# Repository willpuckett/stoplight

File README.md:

# 🚥 Stoplight

### Features

- TMC2209 Stepper Driver
- 1 Ω Sense Resistors (tuned for small motors)
- HUSB238 PD Controller for dynamic Voltage Control
- On-board temperature sensing

Stoplight is a Xiao shield for operating small stepper motors. It is designed
specifically for 28-BYJ48, although it _may_ work with other small (0.225 RMS Amps or less) steppers as
well. It aims to provide utility all around the home, and is especially useful
when working with blinds and knobs.

Commercial stepsticks have sense resistors that are not properly sized for
'smaller' motors to take advantage of TMC2209's features, including
stallguard.

> StopLight brings stall sensing to commodity/low cost, high torque motors.

Stoplight seeks to remedy these issues, while also providing software selectable
voltage control and temperature measurement in a package that works well with
HomeAssistant/ESPHome.

### Todo 

- [ ] TVS Protection
- [ ] Change C14 to same as C18 (BOM Consolidation)
- [ ] Consider removing DIAG and just using UART events instead
- [ ] Consider reconneacting fan port
- [ ] Address DS18B20U reading high 
- [ ] Test fit in mini blind housing
- [ ] Dim LED brightness
- [x] Test StallGuard tuning
  - ✅ works very well at 12v+
  - ⚠️ 9v is untested 
  - 🚦 5v is more finicky
- [x] Add esphome sample yaml's

## Homing

## Fabrication

Use the [production files](jlcpcb/production_files/) to upload to jlc. Or first run [available here](https://octule.com/listing/1891073906/stoplight).

You'll need to swap the motor wires to a JST XH 4 pin housing. In addition to
removing the red cable, you also **must** perform the
[bipolar mod](https://ardufocus.com/howto/28byj-48-bipolar-hw-mod/) on your
steppers.

## Example HomeAssistant Config

The build sometimes fails, but can usually be completed by repeatedly pressing
'Retry', or switching to 'arduino' framework.

### Tuning

<details><summary>This demo exposes a number of controls to make tuning StallGuard easier.</summary>

```yaml
substitutions:
  name: "stoplight"
  friendly_name: "StopLight"
  board: "seeed_xiao_esp32c3"

# board/wifi/ota stuff
packages:
  device_base: !include .esp32.yaml

esp32:
  framework:
    type: esp-idf

logger:
  level: DEBUG

esphome:
  on_boot:
    - tmc2209.configure:
        direction: cw # or ccw
        microsteps: 1
        interpolation: True
        enable_spreadcycle: False
        tcool_threshold: 0
        tpwm_threshold: 0
    - tmc2209.stallguard:
        threshold: 23
    - tmc2209.currents:
        standstill_mode: freewheeling
        run_current: 0.150 # was 0.240
        hold_current: 0
    - button.press: home # home right after boot

external_components:
  - source: github://slimcdk/esphome-custom-components
    components: [tmc2209_hub, tmc2209, stepper]
  - source: github://pr#6693
    components: [husb238]

globals:
  - id: has_homed
    type: bool
    initial_value: "true"
    restore_value: no
  - id: homing_speed
    type: int
    initial_value: "480"
    restore_value: True

web_server:
  port: 80

i2c:
  sda: GPIO6
  scl: GPIO7
  frequency: 800kHz

uart:
  tx_pin: GPIO21
  rx_pin: GPIO20
  baud_rate: 500000 # 9600 -> 500k

one_wire:
  - platform: gpio
    pin: GPIO10

stepper:
  - platform: tmc2209
    id: driver
    # https://www.klipper3d.org/TMC_Drivers.html#limitations
    max_speed: 2000 steps/s # was 4000
    acceleration: 1000 steps/s^2 # was 2500
    deceleration: 1000 steps/s^2 # was 2500
    index_pin: GPIO3
    diag_pin: GPIO4
    rsense: 1000 mOhm
    config_dump_include_registers: False
    vsense: False
    analog_current_scale: False
    on_stall:
      - logger.log: "Motor stalled!"
      - if:
          condition:
            lambda: return !id(has_homed);
          then:
            - stepper.stop: driver
            - tmc2209.configure:
                direction: cw # or ccw
                microsteps: 1
                interpolation: True
                enable_spreadcycle: False
                tcool_threshold: 0
            - stepper.report_position:
                id: driver
                position: 0
            - globals.set:
                id: has_homed
                value: "true"
            - logger.log: "Home position set"
            - tmc2209.disable
    on_status:
      - logger.log:
          format: "Driver is reporting an update! (code %d)"
          args: ["code"]
      - if:
          condition:
            lambda: return code == tmc2209::DIAG_TRIGGERED;
          then:
            - logger.log: DIAG_TRIGGERED
      - if:
          condition:
            lambda: return code == tmc2209::DIAG_TRIGGER_CLEARED;
          then:
            - logger.log: DIAG_TRIGGER_CLEARED
      - if:
          condition:
            lambda: return code == tmc2209::RESET;
          then:
            - logger.log: RESET
      - if:
          condition:
            lambda: return code == tmc2209::RESET_CLEARED;
          then:
            - logger.log: RESET_CLEARED
      - if:
          condition:
            lambda: return code == tmc2209::DRIVER_ERROR;
          then:
            - logger.log: DRIVER_ERROR
      - if:
          condition:
            lambda: return code == tmc2209::DRIVER_ERROR_CLEARED;
          then:
            - logger.log: DRIVER_ERROR_CLEARED
      - if:
          condition:
            lambda: return code == tmc2209::CP_UNDERVOLTAGE;
          then:
            - logger.log: CP_UNDERVOLTAGE
      - if:
          condition:
            lambda: return code == tmc2209::CP_UNDERVOLTAGE_CLEARED;
          then:
            - logger.log: CP_UNDERVOLTAGE_CLEARED
      - if:
          condition:
            lambda: return code == tmc2209::OVERTEMPERATURE_PREWARNING;
          then:
            - logger.log: OVERTEMPERATURE_PREWARNING
      - if:
          condition:
            lambda: return code == tmc2209::OVERTEMPERATURE_PREWARNING_CLEARED;
          then:
            - logger.log: OVERTEMPERATURE_PREWARNING_CLEARED
      - if:
          condition:
            lambda: return code == tmc2209::OVERTEMPERATURE;
          then:
            - logger.log: OVERTEMPERATURE
      - if:
          condition:
            lambda: return code == tmc2209::OVERTEMPERATURE_CLEARED;
          then:
            - logger.log: OVERTEMPERATURE_CLEARED
      - if:
          condition:
            lambda: return code == tmc2209::TEMPERATURE_ABOVE_120C;
          then:
            - logger.log: TEMPERATURE_ABOVE_120C
      - if:
          condition:
            lambda: return code == tmc2209::TEMPERATURE_BELOW_120C;
          then:
            - logger.log: TEMPERATURE_BELOW_120C
      - if:
          condition:
            lambda: return code == tmc2209::TEMPERATURE_ABOVE_143C;
          then:
            - logger.log: TEMPERATURE_ABOVE_143C
      - if:
          condition:
            lambda: return code == tmc2209::TEMPERATURE_BELOW_143C;
          then:
            - logger.log: TEMPERATURE_BELOW_143C
      - if:
          condition:
            lambda: return code == tmc2209::TEMPERATURE_ABOVE_150C;
          then:
            - logger.log: TEMPERATURE_ABOVE_150C
      - if:
          condition:
            lambda: return code == tmc2209::TEMPERATURE_BELOW_150C;
          then:
            - logger.log: TEMPERATURE_BELOW_150C
      - if:
          condition:
            lambda: return code == tmc2209::TEMPERATURE_ABOVE_157C;
          then:
            - logger.log: TEMPERATURE_ABOVE_157C
      - if:
          condition:
            lambda: return code == tmc2209::TEMPERATURE_BELOW_157C;
          then:
            - logger.log: TEMPERATURE_BELOW_157C
      - if:
          condition:
            lambda: return code == tmc2209::OPEN_LOAD;
          then:
            - logger.log: OPEN_LOAD
      - if:
          condition:
            lambda: return code == tmc2209::OPEN_LOAD_CLEARED;
          then:
            - logger.log: OPEN_LOAD_CLEARED
      - if:
          condition:
            lambda: return code == tmc2209::OPEN_LOAD_A;
          then:
            - logger.log: OPEN_LOAD_A
      - if:
          condition:
            lambda: return code == tmc2209::OPEN_LOAD_A_CLEARED;
          then:
            - logger.log: OPEN_LOAD_A_CLEARED
      - if:
          condition:
            lambda: return code == tmc2209::OPEN_LOAD_B;
          then:
            - logger.log: OPEN_LOAD_B
      - if:
          condition:
            lambda: return code == tmc2209::OPEN_LOAD_B_CLEARED;
          then:
            - logger.log: OPEN_LOAD_B_CLEARED
      - if:
          condition:
            lambda: return code == tmc2209::LOW_SIDE_SHORT;
          then:
            - logger.log: LOW_SIDE_SHORT
      - if:
          condition:
            lambda: return code == tmc2209::LOW_SIDE_SHORT_CLEARED;
          then:
            - logger.log: LOW_SIDE_SHORT_CLEARED
      - if:
          condition:
            lambda: return code == tmc2209::LOW_SIDE_SHORT_A;
          then:
            - logger.log: LOW_SIDE_SHORT_A
      - if:
          condition:
            lambda: return code == tmc2209::LOW_SIDE_SHORT_A_CLEARED;
          then:
            - logger.log: LOW_SIDE_SHORT_A_CLEARED
      - if:
          condition:
            lambda: return code == tmc2209::LOW_SIDE_SHORT_B;
          then:
            - logger.log: LOW_SIDE_SHORT_B
      - if:
          condition:
            lambda: return code == tmc2209::LOW_SIDE_SHORT_B_CLEARED;
          then:
            - logger.log: LOW_SIDE_SHORT_B_CLEARED
      - if:
          condition:
            lambda: return code == tmc2209::GROUND_SHORT;
          then:
            - logger.log: GROUND_SHORT
      - if:
          condition:
            lambda: return code == tmc2209::GROUND_SHORT_CLEARED;
          then:
            - logger.log: GROUND_SHORT_CLEARED
      - if:
          condition:
            lambda: return code == tmc2209::GROUND_SHORT_A;
          then:
            - logger.log: GROUND_SHORT_A
      - if:
          condition:
            lambda: return code == tmc2209::GROUND_SHORT_A_CLEARED;
          then:
            - logger.log: GROUND_SHORT_A_CLEARED
      - if:
          condition:
            lambda: return code == tmc2209::GROUND_SHORT_B;
          then:
            - logger.log: GROUND_SHORT_B
      - if:
          condition:
            lambda: return code == tmc2209::GROUND_SHORT_B_CLEARED;
          then:
            - logger.log: GROUND_SHORT_B_CLEARED

button:
  - platform: template
    name: Home
    id: home
    on_press:
      - logger.log: "Going home!"
      - tmc2209.configure:
          direction: cw # or ccw
          microsteps: 1
          interpolation: True
          enable_spreadcycle: False
          tcool_threshold: 104
          tpwm_threshold: 0
      # - lambda: id(driver)->write_register(TPWMTHRS, 0);
      # - lambda: id(driver)->write_register(TCOOLTHRS, 1048575);
      - globals.set:
          id: has_homed
          value: "false"
      - stepper.set_speed:
          id: driver
          # 60 to 300 rpm
          speed: !lambda return id(homing_speed);
      - stepper.set_target:
          id: driver
          target: -9999999
  - platform: template
    name: Stop
    id: stop
    on_press:
      - logger.log: "Stopping!"
      - stepper.stop: driver
      - tmc2209.disable
  - platform: template
    name: 1000 Steps forward
    on_press:
      - logger.log: "Going forward!"
      - stepper.set_speed:
          id: driver
          speed: 400 steps/s
      - stepper.set_target:
          id: driver
          target: !lambda return id(driver)->current_position +1000;
      # - tmc2209.disable

husb238:
  id: husb_01

binary_sensor:
  - platform: husb238
    attached: "PD Attached"

  - platform: template
    name: "Has Homed"
    lambda: return id(has_homed);

text_sensor:
  - platform: husb238
    status: "Last request status"
    capabilities: "Capabilities"

select:
  - platform: husb238
    voltage: "Voltage selector"

sensor:
  - platform: husb238
    voltage: "Contracted Voltage"
    current: "Contracted Current"
    selected_voltage: "Selected Voltage"

  - platform: dallas_temp
    name: temperature

  - platform: tmc2209
    type: stallguard_result
    name: Driver stallguard
    update_interval: 10s

  - platform: tmc2209
    type: actual_current
    name: Actual current
    update_interval: 10s

  - platform: tmc2209
    type: motor_load
    name: Motor load
    update_interval: 10s

  # - platform: tmc2209
  #   type: pwm_scale_sum
  #   name: PWM Scale Sum
  #   update_interval: 250ms

  # - platform: tmc2209
  #   type: pwm_scale_auto
  #   name: PWM Scale Auto
  #   update_interval: 250ms

  # - platform: tmc2209
  #   type: pwm_ofs_auto
  #   name: PWM OFS Auto
  #   update_interval: 250ms

  # - platform: tmc2209
  #   type: pwm_grad_auto
  #   name: PWM Grad Auto
  #   update_interval: 250ms

number:
  - platform: template
    name: Target position
    min_value: -999999
    max_value: 999999
    step: 100
    lambda: return id(driver)->current_position;
    update_interval: 10s
    set_action:
      - stepper.set_target:
          id: driver
          target: !lambda "return x;"

  - platform: template
    name: Homing RPM
    min_value: 0
    max_value: 300
    step: 1
    lambda: return id(homing_speed) * 60 / 32;
    update_interval: 10s
    set_action:
      - globals.set:
          id: homing_speed
          value: !lambda "return x * 32 / 60;"

  - platform: template
    name: SGTHRS
    min_value: 0
    max_value: 255
    step: 1
    lambda: return id(driver)->read_register(SGTHRS);
    update_interval: 10s
    set_action:
      - lambda: id(driver)->write_register(SGTHRS, x);

  - platform: template
    name: TCOOLTHRS
    min_value: 0
    max_value: 1048575
    step: 1
    lambda: return id(driver)->read_register(TCOOLTHRS);
    update_interval: 10s
    set_action:
      - lambda: id(driver)->write_register(TCOOLTHRS, x);

  - platform: template
    name: "Run Current"
    min_value: 0
    max_value: 31
    step: 1
    lambda: return id(driver)->read_field(IRUN_FIELD);
    update_interval: 10s
    set_action:
      - tmc2209.currents:
          irun: !lambda "return x;"
```
</details>

### Wall Heater

<details><summary>This demo implements a knob controlled wall heater.</summary>

```yaml
substitutions:
  name: "heater"
  friendly_name: "Wall Heater"
  board: "seeed_xiao_esp32c3"

# board/wifi/ota stuff
packages:
  device_base: !include .esp32.yaml

esphome:
  on_boot:
    # - lambda: id(husb_01)->command_request_voltage(5);
    - tmc2209.configure:
        direction: cw # or ccw
        microsteps: 1
        interpolation: True
        enable_spreadcycle: False
        tcool_threshold: 0
        tpwm_threshold: 0
    - tmc2209.stallguard:
        threshold: 23
    - tmc2209.currents:
        standstill_mode: freewheeling
        run_current: 0.1375 # was 0.150
        hold_current: 0
    - button.press: probe_low # home right after boot

external_components:
  - source: github://slimcdk/esphome-custom-components
    components: [ tmc2209_hub, tmc2209, stepper ]
  - source: github://pr#6693
    components: [ husb238 ]

globals:
  - id: steps
    type: int
    restore_value: yes
    initial_value: "1000"

i2c:
  sda: GPIO6
  scl: GPIO7 
  frequency: 800kHz

uart:
  tx_pin: GPIO21
  rx_pin: GPIO20
  baud_rate: 500000 # 9600 -> 500k

one_wire:
  - platform: gpio
    pin: GPIO10

husb238:
  id: husb_01

stepper:
  - platform: tmc2209
    id: driver
    max_speed: 480 steps/s
    acceleration: 1000 steps/s^2 
    deceleration: 1000 steps/s^2 
    index_pin: GPIO3
    diag_pin: GPIO4
    rsense: 1000 mOhm
    on_stall:
      - stepper.stop: driver
      - logger.log: Endstop Detected 🍍

script:
  - id: move_stepper
    mode: restart
    parameters:
      # use 0/false for low side endstop, 1/true for high side
      homing: bool
      target: int
    then:
      - lambda: id(husb_01)->command_request_voltage(20);
      - tmc2209.configure:
          tcool_threshold: !lambda 'return homing ? 104 : 0;'
      - stepper.set_speed:
          id: driver
          speed: 480 steps/s
      - delay: 1s
      - stepper.set_target:
          id: driver
          target: !lambda 'return target;'
      - wait_until:
          condition:
            lambda: 'return id(driver)->has_reached_target();'
      - logger.log:
          format: "Moved to %d steps"
          args: [ 'id(driver)->current_position' ]
      - tmc2209.disable:
          id: driver 
      - lambda: id(husb_01)->command_request_voltage(5);

button:
  - platform: template
    name: Probe Low
    id: probe_low 
    on_press:
      - climate.control:
          id: pid_climate
          mode: 'OFF'
      - script.execute: 
          id: move_stepper
          homing: true
          target: -9999999
      - script.wait: move_stepper
      - stepper.report_position:
          id: driver
          position: 0
      - logger.log:
          format: "Probed to %d steps"
          args: [ 'id(driver)->current_position' ]
      
  - platform: template
    name: Probe High
    id: probe_high
    on_press:
      - climate.control:
          id: pid_climate
          mode: 'OFF'
      - script.execute: 
          id: move_stepper
          homing: true
          target: 9999999
      - script.wait: move_stepper
      - globals.set:
          id: steps
          value: !lambda 'return id(driver)->current_position;'
 
  - platform: template
    name: "PID Climate Autotune"
    on_press:
      - climate.pid.autotune: pid_climate

sensor:
  - platform: husb238
    voltage: "Contracted Voltage"

  - platform: template
    name: "Steps"
    id: steps_display
    icon: "mdi:shoe-print"
    accuracy_decimals: 0
    lambda: 'return id(steps);'

  - platform: dallas_temp
    id: ds_temp
    filters: 
      - lambda: return x - 13.5;

  # This sensor takes the output from the pid heater and transforms it to step numbers
  - platform: pid
    name: "PID Climate Heat"
    id: heat_float
    type: HEAT
    filters:
      - round_to_multiple_of: 10
      - delta: 9
    on_value:
      then:
        - script.execute: 
            id: move_stepper
            homing: false
            target: !lambda 'return static_cast<int>(id(steps) * (x / 100));'

# This is just a fake output to make the pid heater happy.
# Ideally, the pin will use the onboard led, but I'm not sure what the pin number is for that...
output:
  - platform: ledc
    pin: GPIO2
    id: heater_output

# Example configuration entry
climate:
  - platform: pid
    name: "PID Climate Controller"
    id: pid_climate
    sensor: ds_temp
    default_target_temperature: 21°C
    heat_output: heater_output
    control_parameters:
      kp: 4
      ki: 0.4
      kd: 0.5
      output_averaging_samples: 5      # smooth the output over 5 samples
      derivative_averaging_samples: 5  # smooth the derivative value over 5 samples
    # deadband_parameters:
    #   threshold_high: 0.5°C
    #   threshold_low: -1.0°C
    #   kp_multiplier: 0.5   # proportional gain reduced inside deadband
    #   ki_multiplier: 0.25   # integral accumulates at only 25% of normal ki
    #   kd_multiplier: 0.5   # derviative is reduced inside deadband
    #   deadband_output_averaging_samples: 5   # average the output over 15 samples within the deadband
```

</details>

### Blinds

<details><summary>StallGuard blinds operation</summary>

```yaml
substitutions:
  name: "blins03"
  blind_number: right
  friendly_name: "Right Blind"
  board: "seeed_xiao_esp32c3"
  delay: "1s"

# board/wifi/ota stuff
packages:
  device_base: !include .esp32.yaml

esphome:
  on_boot:
    - tmc2209.configure:
        direction: ccw # or ccw
        microsteps: 1
        interpolation: True
        enable_spreadcycle: False
        tcool_threshold: 0
        tpwm_threshold: 0
    - tmc2209.stallguard:
        threshold: 45 
    - tmc2209.currents:
        standstill_mode: freewheeling
        run_current: 0.1375 # was 0.150
        hold_current: 0

external_components:
  - source: github://slimcdk/esphome-custom-components
    components: [ tmc2209_hub, tmc2209, stepper ]
  - source: github://pr#6693
    components: [ husb238 ]

globals:
  - id: steps
    type: int
    restore_value: yes
    initial_value: "1000"

i2c:
  sda: GPIO6
  scl: GPIO7 
  frequency: 800kHz

uart:
  tx_pin: GPIO21
  rx_pin: GPIO20
  baud_rate: 500000 # 9600 -> 500k

one_wire:
  - platform: gpio
    pin: GPIO10

husb238:
  id: husb_01

stepper:
  - platform: tmc2209
    id: driver
    max_speed: 480 steps/s
    acceleration: 1000 steps/s^2 
    deceleration: 1000 steps/s^2 
    index_pin: GPIO3
    diag_pin: GPIO4
    rsense: 1000 mOhm
    on_stall:
      - stepper.stop: driver
      - logger.log: Endstop Detected 🍍

script:
  - id: move_stepper
    mode: restart
    parameters:
      # use 0/false for low side endstop, 1/true for high side
      homing: bool
      target: int
    then:
      - lambda: id(husb_01)->command_request_voltage(12);
      - tmc2209.configure:
          tcool_threshold: !lambda 'return homing ? 104 : 0;'
      - stepper.set_speed:
          id: driver
          speed: !lambda 'return homing ? 480 : 120;'
      - delay: 1s
      - stepper.set_target:
          id: driver
          target: !lambda 'return target;'
      - while:
          condition:
            lambda: 'return !id(driver)->has_reached_target();'
          then:
            - cover.template.publish:
                id: ${name}_${blind_number}
                position: !lambda 'return float( id(driver).current_position ) / float( id(steps) );' 
                current_operation: !lambda 'return id(driver).current_position < id(driver).target_position ? COVER_OPERATION_OPENING : COVER_OPERATION_CLOSING;'
            - delay: ${delay}
      - logger.log:
          format: "Moved to %d steps"
          args: [ 'id(driver)->current_position' ]
      - tmc2209.disable:
          id: driver 
      - lambda: id(husb_01)->command_request_voltage(5);
      - cover.template.publish:
          id: ${name}_${blind_number}
          position: !lambda 'return float( id(driver).current_position ) / float( id(steps) );' 
          current_operation: IDLE

button:
  - platform: template
    name: Probe Low
    id: probe_low 
    on_press:
      - script.execute: 
          id: move_stepper
          homing: true
          target: -9999999
      - script.wait: move_stepper
      - stepper.report_position:
          id: driver
          position: 0
      - logger.log:
          format: "Probed to %d steps"
          args: [ 'id(driver)->current_position' ]
      
  - platform: template
    name: Probe High
    id: probe_high
    on_press:
      - script.execute: 
          id: move_stepper
          homing: true
          target: 9999999
      - script.wait: move_stepper
      - globals.set:
          id: steps
          value: !lambda 'return id(driver)->current_position;'

sensor:
  - platform: husb238
    voltage: "Contracted Voltage"

  - platform: template
    name: "Steps"
    id: steps_display
    icon: "mdi:shoe-print"
    accuracy_decimals: 0
    lambda: 'return id(steps);'

  - platform: dallas_temp
    id: ds_temp
    filters: 
      - lambda: return x - 13.5;

cover:
  - platform: template
    name: "${blind_number}"
    id: ${name}_${blind_number}
    open_action:
      then:
        - logger.log: "Opening"
        - button.press: probe_high
    close_action:
      then:
        - logger.log: "Closing"
        - button.press: probe_low
    position_action:
      then:
        - logger.log: "Jostling"
        - script.execute: 
            id: move_stepper
            homing: false
            target: !lambda return int(id(steps) * pos);
    stop_action:
      then:
        - script.execute: 
            id: move_stepper
            homing: false
            target: !lambda return id(driver).current_position;
    has_position: true
    device_class: blind

switch:
  - platform: template
    name: "Reset ${blind_number}"
    id: reset_${name}_${blind_number}
    turn_on_action:
      - button.press: probe_low
      - script.wait: move_stepper
      - button.press: probe_high
      - script.wait: move_stepper
      - button.press: probe_low
      - script.wait: move_stepper
      - switch.turn_off: reset_${name}_${blind_number}
```

</details>

## Schematic

## Reference

[TMC2209 Calaulations Worksheet](https://www.analog.com/media/en/engineering-tools/design-tools/TMC2209_Calculations.xlsx)

[BTT-TMC2209-v1.2](https://pax.deno.dev/bigtreetech/BIGTREETECH-TMC2209-V1.2@master/Schematic/TMC2209-V1.2.pdf?b)

[Cookie Robotics](https://cookierobotics.com/042/)

[jangeox](http://www.jangeox.be/2013/10/change-unipolar-28byj-48-to-bipolar.html)

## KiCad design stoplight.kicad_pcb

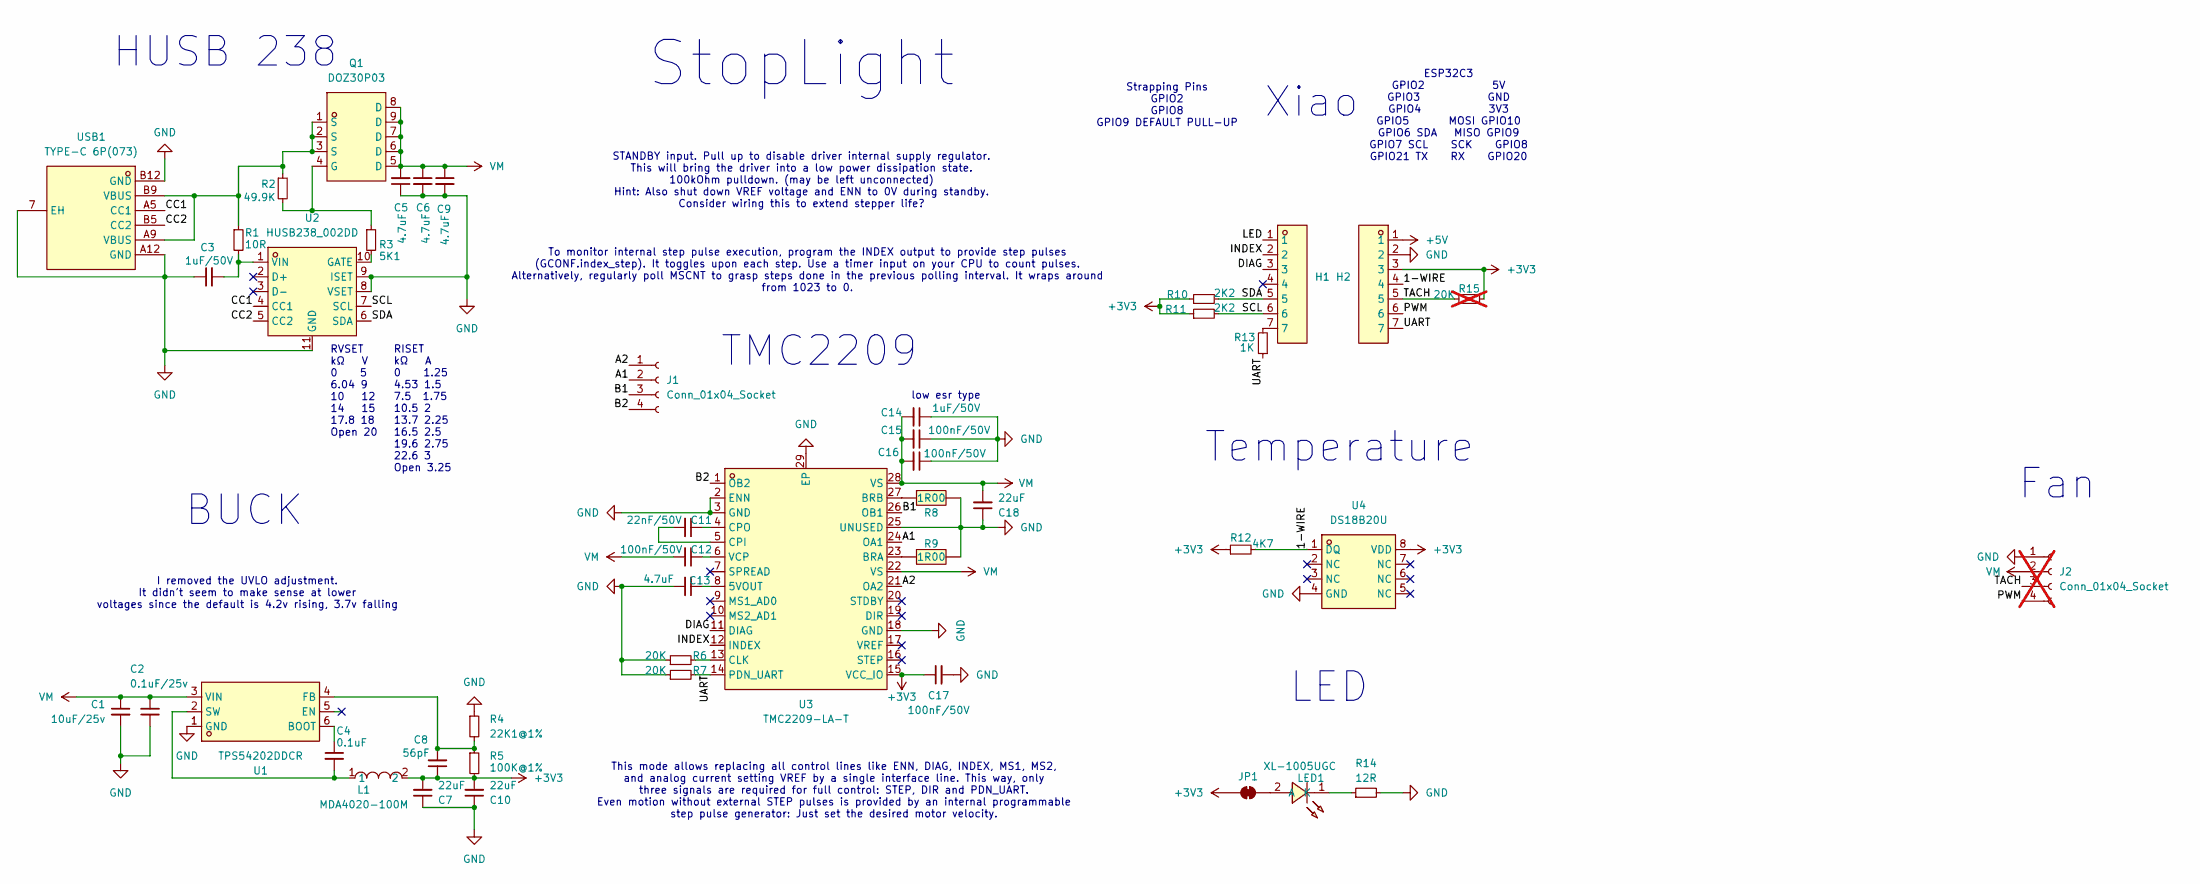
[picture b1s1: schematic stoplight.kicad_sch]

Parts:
C1: 10uF/25v; C_1210_3225Metric; LCSC C2918502
C2: 0.1uF/25v; C_0603_1608Metric; LCSC C3011652
C3: 1uF/50V; C_0805_2012Metric; LCSC C215803
C4: 0.1uF; C_0402_1005Metric; LCSC C77020
C5, C6, C9: 4.7uF; C_0805_2012Metric; LCSC C2991173
C7, C10, C18: 22uF; C_0805_2012Metric; LCSC Part C6119901
C8: 56pF; C_0402_1005Metric; LCSC C107007
C11: 22nF/50V; C_0402_1005Metric; LCSC C77023
C12, C15, C16, C17: 100nF/50V; C_0402_1005Metric; LCSC C77020
C13: 4.7uF; C_0603_1608Metric; LCSC C913474
C14: 1uF/50V; C_0603_1608Metric; LCSC C90540
H1, H2: MF254V-11-07-0743; HDR-TH_7P-P2.54-V-F_MF254V-11-07-0743; LCSC Part C2889988
J1: Conn_01x04_Socket; JST_XH_B4B-XH-A_1x04_P2.50mm_Vertical; LCSC C23398778
J2: Conn_01x04_Socket; FanPinHeader_1x04_P2.54mm_Vertical; not fitted
JP1: SolderJumper_2_Bridged; Solder_Jumper_Tight
L1: MDA4020-100M; IND-SMD_L4.5-W4.1_YXMAA0402; LCSC Part C2847473
LED1: XL-1005UGC; LED0402-RD_GREEN; LCSC Part C965793
Q1: DOZ30P03; PDFN-8_L3.1-W3.0-P0.65-LS3.3-BL; LCSC Part C36499166
R1: 10R; R_0603_1608Metric; LCSC C109318
R2: 49.9K; R_0603_1608Metric; LCSC C2930109
R3: 5K1; R_0603_1608Metric; LCSC C23186
R4: 22K1@1%; R_0402_1005Metric; LCSC C163478
R5: 100K@1%; R_0402_1005Metric; LCSC C60491
R6, R7: 20K; R_0402_1005Metric; LCSC C93942
R8, R9: 1R00; R0805; LCSC Part C346776
R10, R11: 2K2; R_0402_1005Metric; LCSC C114762
R12: 4K7; R_0402_1005Metric; LCSC C105871
R13: 1K; R_0603_1608Metric; LCSC C22548
R14: 12R; R_0402_1005Metric; LCSC Part C2909317
R15: 20K; R_0402_1005Metric; not fitted
U1: TPS54202DDCR; SOT-23-6_L2.9-W1.6-P0.95-LS2.8-BL; LCSC Part C191884
U2: HUSB238_002DD; DFN-10_L3.0-W3.0-P0.50-BL-EP2.5; LCSC Part C7471904
U3: TMC2209-LA-T; QFN-28_L5.0-W5.0-P0.50-BL-EP; LCSC Part C2150710
U4: DS18B20U; MSOP-8_L3.0-W3.0-P0.65-LS4.9-BL; LCSC Part C695836
USB1: TYPE-C 6P(073); TYPE-C-SMD_TYPE-C-6P_5; LCSC Part C668623

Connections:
+3V3: C7.2, C8.1, C10.2, C17.1, H2.3, JP1.1 (A), L1.2, R5.2, R10.1, R11.1, R12.1, R15.2, U3.15 (VCC_IO), U4.8 (VDD)
+5V: H2.1
/1-WIRE: H2.4, R12.2, U4.1 (DQ)
/A1: J1.2, U3.24 (OA1)
/A2: J1.1, U3.21 (OA2)
/B1: J1.3, U3.26 (OB1)
/B2: J1.4, U3.1 (OB2)
/CC1: U2.4 (CC1), USB1.A5 (CC1)
/CC2: U2.5 (CC2), USB1.B5 (CC2)
/DIAG: H1.3, U3.11 (DIAG)
/INDEX: H1.2, U3.12 (INDEX)
/LED: H1.1
/PWM: H2.6, J2.4
/SCL: H1.6, R11.2, U2.7 (SCL)
/SDA: H1.5, R10.2, U2.6 (SDA)
/TACH: H2.5, J2.3, R15.1
/UART: H2.7, R7.2, R13.1, U3.14 (PDN_UART)
GND: C1.2, C2.1, C3.1, C5.1, C6.2, C7.1, C9.2, C10.1, C13.2, C14.1, C15.1, C16.1, C17.2, C18.1, H2.2, J2.1, R4.1, R6.1, R7.1, R8.2, R9.2, R14.2, U1.1 (GND), U2.8 (VSET), U2.9 (ISET), U2.11 (GND), U3.2 (ENN), U3.3 (GND), U3.18 (GND), U3.25 (UNUSED), U3.29 (EP), U4.4 (GND), USB1.7 (EH), USB1.A12 (GND), USB1.B12 (GND)
unnamed: H1.7, R13.2
unnamed: JP1.2 (B), LED1.2 (A)
unnamed: LED1.1 (K), R14.1
unnamed: Q1.4 (G), R2.2, R3.1
unnamed: Q1.1 (S), Q1.2 (S), Q1.3 (S), R1.1, R2.1, USB1.A9 (VBUS), USB1.B9 (VBUS)
unnamed: C4.1, U1.6 (BOOT)
unnamed: C8.2, R4.2, R5.1, U1.4 (FB)
unnamed: C4.2, L1.1, U1.2 (SW)
unnamed: R3.2, U2.10 (GATE)
unnamed: C3.2, R1.2, U2.1 (VIN)
unnamed: C13.1, U3.8 (5VOUT)
unnamed: R9.1, U3.23 (BRA)
unnamed: R8.1, U3.27 (BRB)
unnamed: R6.2, U3.13 (CLK)
unnamed: C11.2, U3.5 (CPI)
unnamed: C11.1, U3.4 (CPO)
unnamed: C12.1, U3.6 (VCP)
VM: C1.1, C2.2, C5.2, C6.1, C9.1, C12.2, C14.2, C15.2, C16.2, C18.2, J2.2, Q1.5 (D), Q1.6 (D), Q1.7 (D), Q1.8 (D), Q1.9 (D), U1.3 (VIN), U3.22 (VS), U3.28 (VS)

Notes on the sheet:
Strapping Pins GPIO2 GPIO8 GPIO9 DEFAULT PULL-UP
Xiao
TMC2209
I removed the UVLO adjustment. It didn't seem to make sense at lower voltages since the default is 4.2v rising, 3.7v falling
STANDBY input. Pull up to disable driver internal supply regulator. This will bring the driver into a low power dissipation state. 100kOhm pulldown. (may be left unconnected) Hint: Also shut down VREF voltage and ENN to 0V during standby. Consider wiring this to extend stepper life?
low esr type
To monitor internal step pulse execution, program the INDEX output to provide step pulses (GCONF.index_step). It toggles upon each step. Use a timer input on your CPU to count pulses. Alternatively, regularly poll MSCNT to grasp steps done in the previous polling interval. It wraps around from 1023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
RVSET kΩ V 0 5 6.04 9 10 12 14 15 17.8 18 Open 20
StopLight
LED
Fan
RISET kΩ A 0 1.25 4.53 1.5 7.5 1.75 10.5 2 13.7 2.25 16.5 2.5 19.6 2.75 22.6 3 Open 3.25
This mode allows replacing all control lines like ENN, DIAG, INDEX, MS1, MS2, and analog current setting VREF by a single interface line. This way, only three signals are required for full control: STEP, DIR and PDN_UART. Even motion without external STEP pulses is provided by an internal programma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
Temperature
HUSB 238
BUCK
ESP32C3 GPIO2 5V GPIO3 GND GPIO4 3V3 GPIO5 MOSI GPIO10 GPIO6 SDA MISO GPIO9 GPIO7 SCL SCK GPIO8 GPIO21 TX RX GPIO20

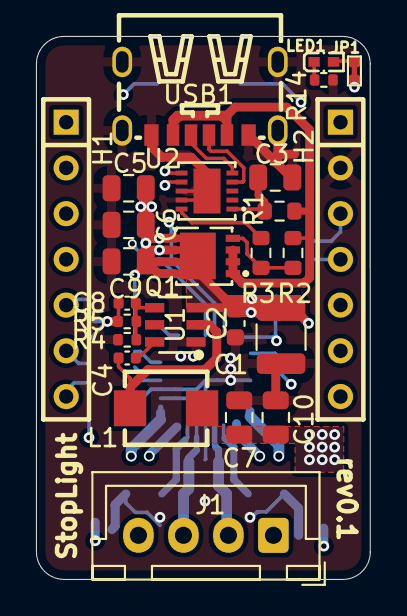
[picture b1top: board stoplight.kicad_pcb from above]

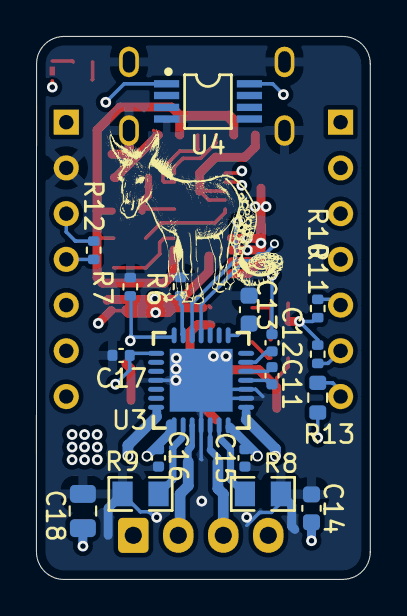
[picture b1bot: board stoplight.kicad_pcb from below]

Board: 4 copper layers, 18.5 x 30.2 mm, 44 parts (18 on the bottom side), 32 nets.

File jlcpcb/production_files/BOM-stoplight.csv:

Comment,Designator,Footprint,LCSC,Quantity
4K7,R12,R_0402_1005Metric,C105871,1
56pF,C8,C_0402_1005Metric,C107007,1
10R,R1,R_0603_1608Metric,C109318,1
2K2,"R10,R11",R_0402_1005Metric,C114762,2
22K1@1%,R4,R_0402_1005Metric,C163478,1
TPS54202DDCR,U1,SOT-23-6_L2.9-W1.6-P0.95-LS2.8-BL,C191884,1
TMC2209-LA-T,U3,QFN-28_L5.0-W5.0-P0.50-BL-EP,C2150710,1
1uF/50V,C3,C_0805_2012Metric,C215803,1
1K,R13,R_0603_1608Metric,C22548,1
5K1,R3,R_0603_1608Metric,C23186,1
Conn_01x04_Socket,J1,JST_XH_B4B-XH-A_1x04_P2.50mm_Vertical,C23398778,1
MDA4020-100M,L1,IND-SMD_L4.5-W4.1_YXMAA0402,C2847473,1
MF254V-11-07-0743,"H1,H2",HDR-TH_7P-P2.54-V-F_MF254V-11-07-0743,C2889988,2
12R,R14,R_0402_1005Metric,C2909317,1
10uF/25v,C1,C_1210_3225Metric,C2918502,1
49.9K,R2,R_0603_1608Metric,C2930109,1
4.7uF,"C5,C6,C9",C_0805_2012Metric,C2991173,3
0.1uF/25v,C2,C_0603_1608Metric,C3011652,1
1R00,"R8,R9",R0805,C346776,2
DOZ30P03,Q1,PDFN-8_L3.1-W3.0-P0.65-LS3.3-BL,C36499166,1
100K@1%,R5,R_0402_1005Metric,C60491,1
22uF,"C10,C18,C7",C_0805_2012Metric,C6119901,3
TYPE-C 6P(073),USB1,TYPE-C-SMD_TYPE-C-6P_5,C668623,1
DS18B20U,U4,MSOP-8_L3.0-W3.0-P0.65-LS4.9-BL,C695836,1
HUSB238_002DD,U2,DFN-10_L3.0-W3.0-P0.50-BL-EP2.5,C7471904,1
100nF/50V,"C12,C15,C16,C17,C4",C_0402_1005Metric,C77020,5
22nF/50V,C11,C_0402_1005Metric,C77023,1
1uF/50V,C14,C_0603_1608Metric,C90540,1
4.7uF,C13,C_0603_1608Metric,C913474,1
20K,"R6,R7",R_0402_1005Metric,C93942,2
XL-1005UGC,LED1,LED0402-RD_GREEN,C965793,1

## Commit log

2025-03-31 change to stoplight
2025-04-01 add power pours and additional vias
2025-04-16 update redme
2025-04-16 trying video again
2025-04-16 again
2025-04-16 add gif to readme
2025-04-16 Add Solderpad Hardware License v2.1
2025-04-16 Add TMC2209 Calculations Worksheet link to references
2025-04-18 add heater example to readme
2025-04-19 add blinds example
2025-04-19 add todo list
2025-04-19 readme edits
2025-04-19 add features
